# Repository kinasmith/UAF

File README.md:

View this project on [CADLAB.io](https://cadlab.io/node/1009). 

# UAF
This is a storage and sharing area for my projects for the University of Alaska Fairbanks. 
Things are likely in disarray, my apologies.

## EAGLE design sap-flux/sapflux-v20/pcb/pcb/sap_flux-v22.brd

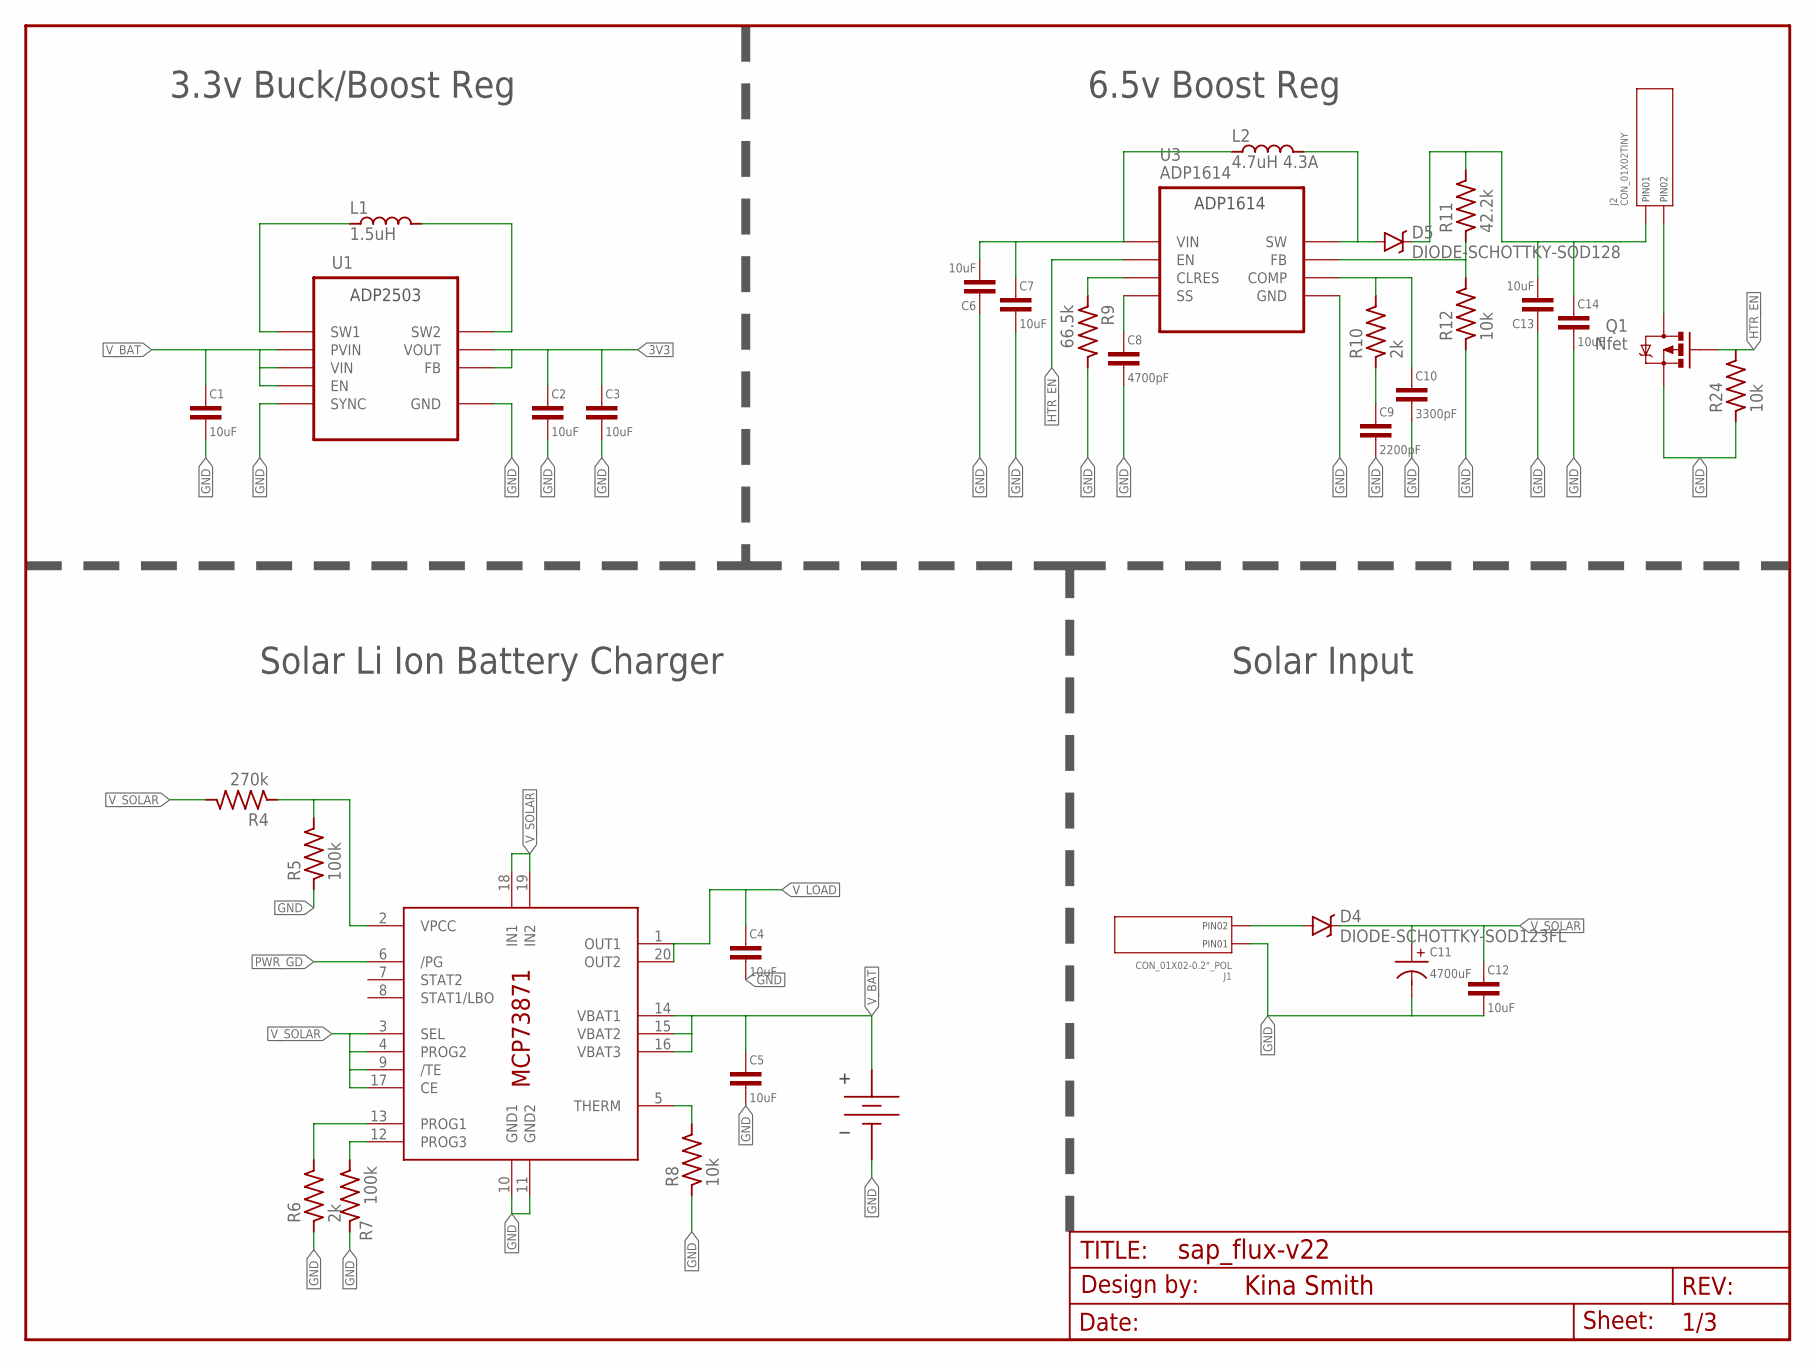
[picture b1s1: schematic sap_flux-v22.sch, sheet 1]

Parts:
BATT1: BATTERY_HOLDER-18650_CLIP; BAT_18650_CLIP
C1, C2, C3, C4, C5, C6, C7, C12, C13, C14: 10uF; C0805-N; PARTNO GRM21BR61C106KE15K
C8: 4700pF; C0603-N; PARTNO GRM188R71C472KA01D
C9: 2200pF; C0603-N; PARTNO GRM188R71C222KA01D
C10: 3300pF; C0603-N; PARTNO C0603C332K4RACTU
C11: 4700uF; CP_TH_5MM
D4: DIODE-SCHOTTKY-SOD123FL; SOD-123FL; PARTNO MBR120VLSFT1G
D5: DIODE-SCHOTTKY-SOD128; SOD128; PARTNO CMS05(TE12L,Q,M)
FRAME1: FRAME-LETTER; CREATIVE_COMMONS
J1: CON_01X02-0.2"_POL; 1X02_SCREWTERM_0.2IN
J2: CON_01X02TINY; 1X02_TINY
L1: 1.5uH; L3030; PARTNO NR3015T1R5N
L2: 4.7uH 4.3A; L8080
Q1: Nfet; SOT23-3; PARTNO DMN2075U-7
R4: 270k; R0603-N; PARTNO RC0603FR-07270KL
R5, R7: 100k; R0603-N; PARTNO RC0603FR-07100KL
R6, R10: 2k; R0603-N; PARTNO RC0603FR-072KL
R8, R12, R24: 10k; R0603-N; PARTNO RC0603FR-0710KL
R9: 66.5k; R0603-N; PARTNO RC0603FR-0766K5L
R11: 42.2k; R0603-N; PARTNO RC0603FR-0742K2L
U1: ADP2503; DFN300X300X80-11N; PARTNO ADP2503ACPZ-3.3-R7
U2: MCP73871; QFN20
U3: ADP1614; DFN300X300X80-11N; PARTNO ADP1614ACPZ-650-R7

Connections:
3V3: C2.1, C3.1, U1.1 (VOUT), U1.10 (FB); also elsewhere on the board
6V5: C13.2, C14.1, D5.C-1 (C), J2.NEG (PIN1), R11.2
6V5_INDUCTOR: D5.A-2 (A), L2.2, U3.6 (SW), U3.7 (SW)
GND: BATT1.NEG_1 (GND), BATT1.NEG_2 (GND), BATT1.NEG_3 (GND), C1.2, C2.2, C3.2, C4.2, C5.2, C6.1, C7.2, C8.2, C9.2, C10.2, C11.NEG, C12.2, C13.1, C14.2, J1.NEG (PIN1), Q1.2 (S), R5.1, R6.1, R7.1, R8.1, R9.2, R12.1, R24.1, U1.3 (GND), U1.7 (SYNC), U1.9 (GND), U1.11 (GND), U2.10 (GND1), U2.11 (GND2), U3.4 (GND), U3.5 (GND), U3.11 (GND); also elsewhere on the board
HTR_EN: Q1.1 (G), R24.2, U3.3 (EN); also elsewhere on the board
unnamed: D4.A, J1.POS (PIN2)
unnamed: R4.1, R5.2, U2.2 (VPCC)
unnamed: R6.2, U2.13 (PROG1)
unnamed: R7.2, U2.12 (PROG3)
unnamed: L1.P$1, U1.4 (SW1)
unnamed: L1.P$2, U1.2 (SW2)
unnamed: R8.2, U2.5 (THERM)
unnamed: J2.POS (PIN2), Q1.3 (D)
unnamed: C8.1, U3.10 (SS)
unnamed: R9.1, U3.9 (CLRES)
unnamed: R11.1, R12.2, U3.2 (FB)
unnamed: C10.1, R10.2, U3.1 (COMP)
unnamed: C9.1, R10.1
PWR_GD: U2.6 (/PG); also elsewhere on the board
V_BAT: BATT1.POS_1 (VBAT), BATT1.POS_2 (VBAT), BATT1.POS_3 (VBAT), C1.1, C5.1, C6.2, C7.1, L2.1, U1.5 (PVIN), U1.6 (EN), U1.8 (VIN), U2.14 (VBAT1), U2.15 (VBAT2), U2.16 (VBAT3), U3.8 (VIN); also elsewhere on the board
V_LOAD: C4.1, U2.1 (OUT1), U2.20 (OUT2)
V_SOLAR: C11.POS, C12.1, D4.C, R4.2, U2.3 (SEL), U2.4 (PROG2), U2.9 (/TE), U2.17 (CE), U2.18 (IN1), U2.19 (IN2)

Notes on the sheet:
3.3v Buck/Boost Reg
6.5v Boost Reg
Solar Li Ion Battery Charger
Solar Input

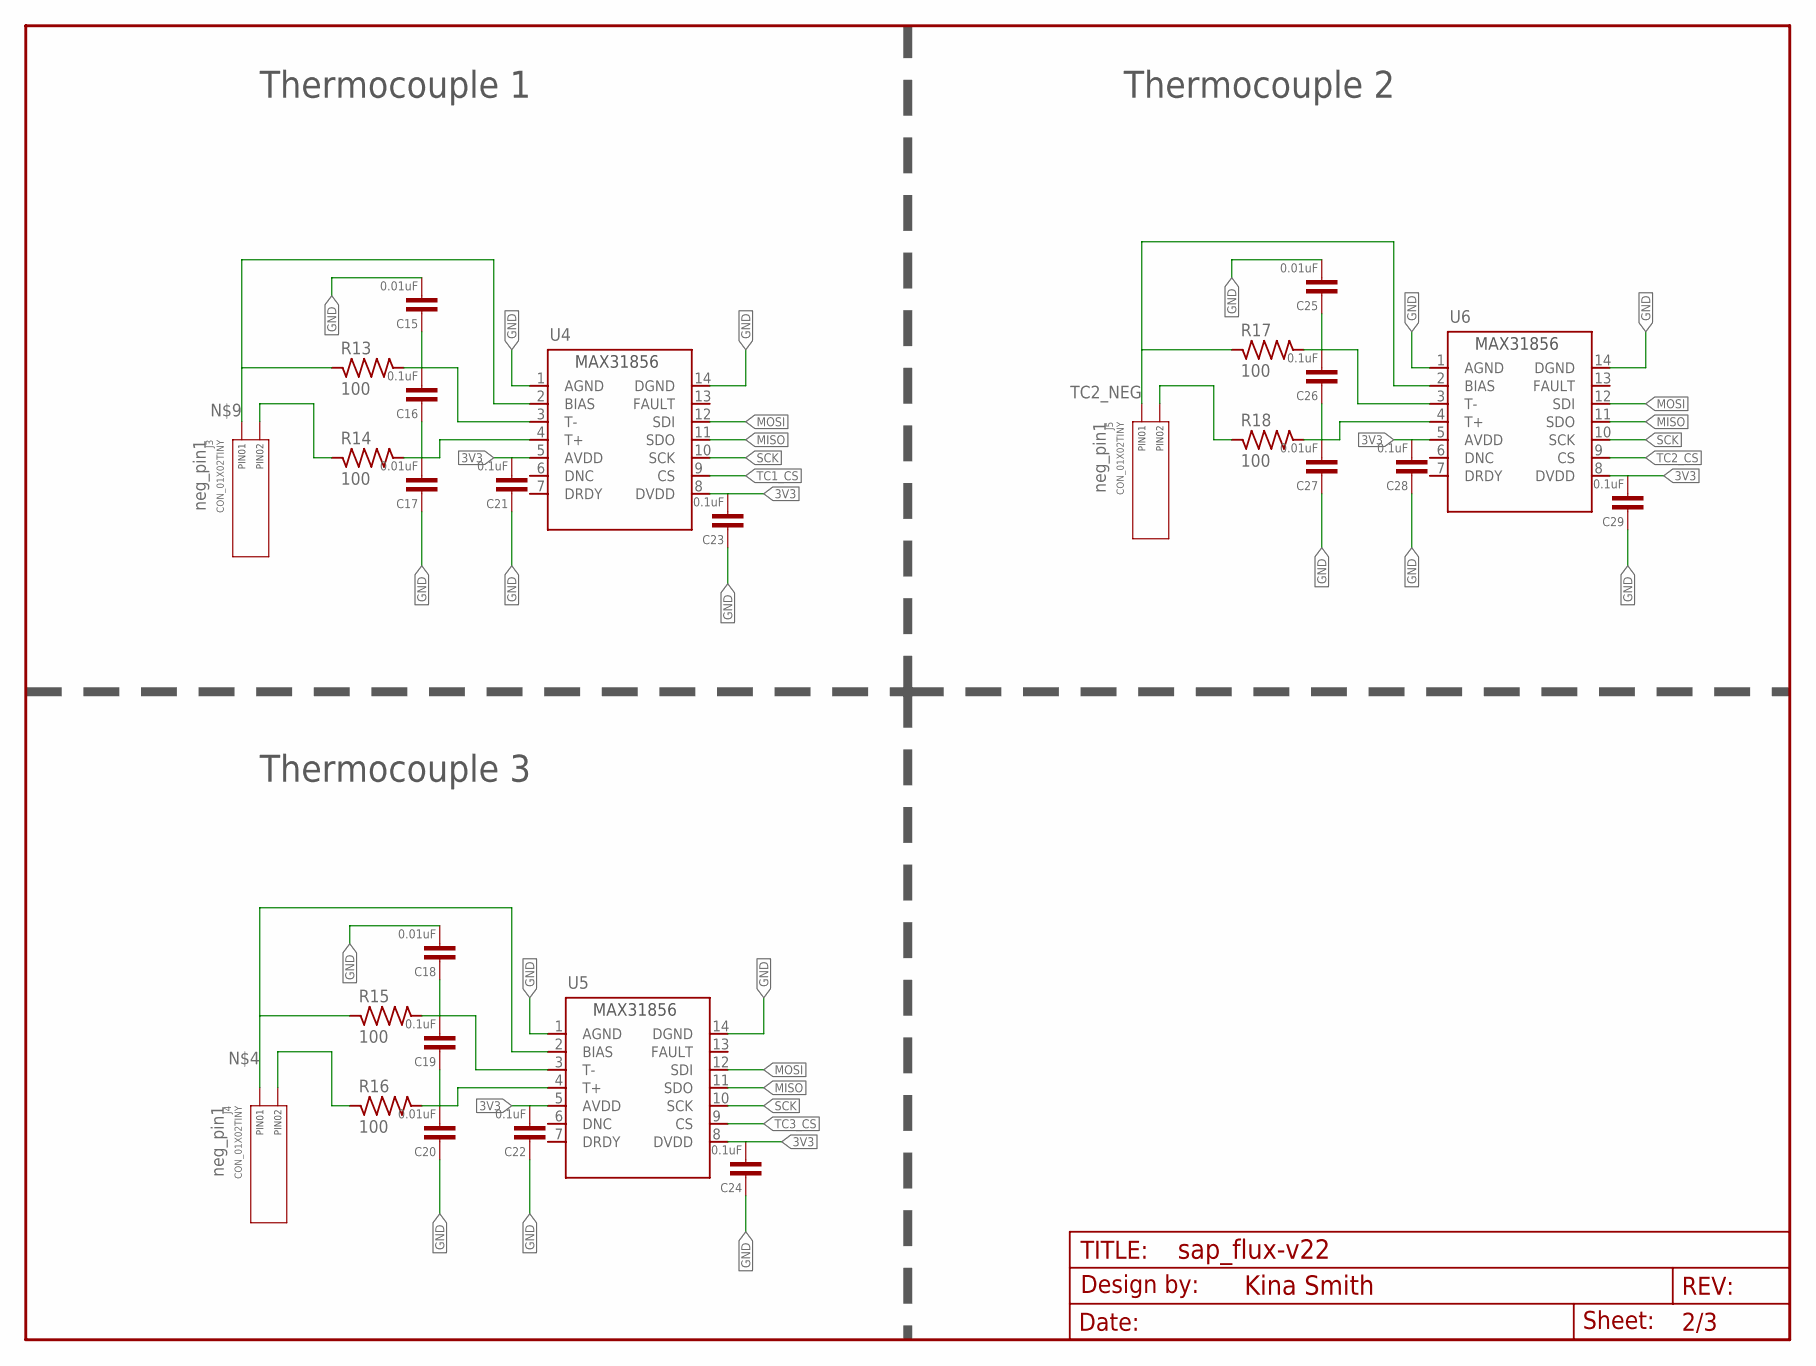
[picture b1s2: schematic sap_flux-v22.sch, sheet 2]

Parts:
C15, C17, C18, C20, C25, C27: 0.01uF; C0603-N; PARTNO GRM188R71C103KA01D
C16, C19, C21, C22, C23, C24, C26, C28, C29: 0.1uF; C0603-N; PARTNO CC0603KRX7R7BB104
FRAME2: FRAME-LETTERNO_PACKAGE; DUMMY
J3, J4, J5: CON_01X02TINY; 1X02_TINY
R13, R14, R15, R16, R17, R18: 100; R0603-N; PARTNO RC0603FR-07100RL
U4, U5, U6: MAX31856MUD+; TSSOP14

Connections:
3V3: C21.2, C22.2, C23.2, C24.2, C28.2, C29.2, U4.5 (AVDD), U4.8 (DVDD), U5.5 (AVDD), U5.8 (DVDD), U6.5 (AVDD), U6.8 (DVDD); also elsewhere on the board
GND: C15.2, C17.1, C18.2, C20.1, C21.1, C22.1, C23.1, C24.1, C25.2, C27.1, C28.1, C29.1, U4.1 (AGND), U4.14 (DGND), U5.1 (AGND), U5.14 (DGND), U6.1 (AGND), U6.14 (DGND); also elsewhere on the board
MISO: U4.11 (SDO), U5.11 (SDO), U6.11 (SDO); also elsewhere on the board
MOSI: U4.12 (SDI), U5.12 (SDI), U6.12 (SDI); also elsewhere on the board
unnamed: J4.POS (PIN2), R16.1
unnamed: J4.NEG (PIN1), R15.1, U5.2 (BIAS)
unnamed: J3.POS (PIN2), R14.1
unnamed: J3.NEG (PIN1), R13.1, U4.2 (BIAS)
unnamed: C19.1, C20.2, R16.2, U5.4 (T+)
unnamed: C18.1, C19.2, R15.2, U5.3 (T-)
unnamed: C16.1, C17.2, R14.2, U4.4 (T+)
unnamed: C15.1, C16.2, R13.2, U4.3 (T-)
unnamed: C25.1, C26.2, R17.2, U6.3 (T-)
unnamed: C26.1, C27.2, R18.2, U6.4 (T+)
SCK: U4.10 (SCK), U5.10 (SCK), U6.10 (SCK); also elsewhere on the board
TC1_CS: U4.9 (CS); also elsewhere on the board
TC2_CS: U6.9 (CS); also elsewhere on the board
TC2_NEG: J5.NEG (PIN1), R17.1, U6.2 (BIAS)
TC2_POS: J5.POS (PIN2), R18.1
TC3_CS: U5.9 (CS); also elsewhere on the board

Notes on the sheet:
Thermocouple 3
Thermocouple 1
Thermocouple 2

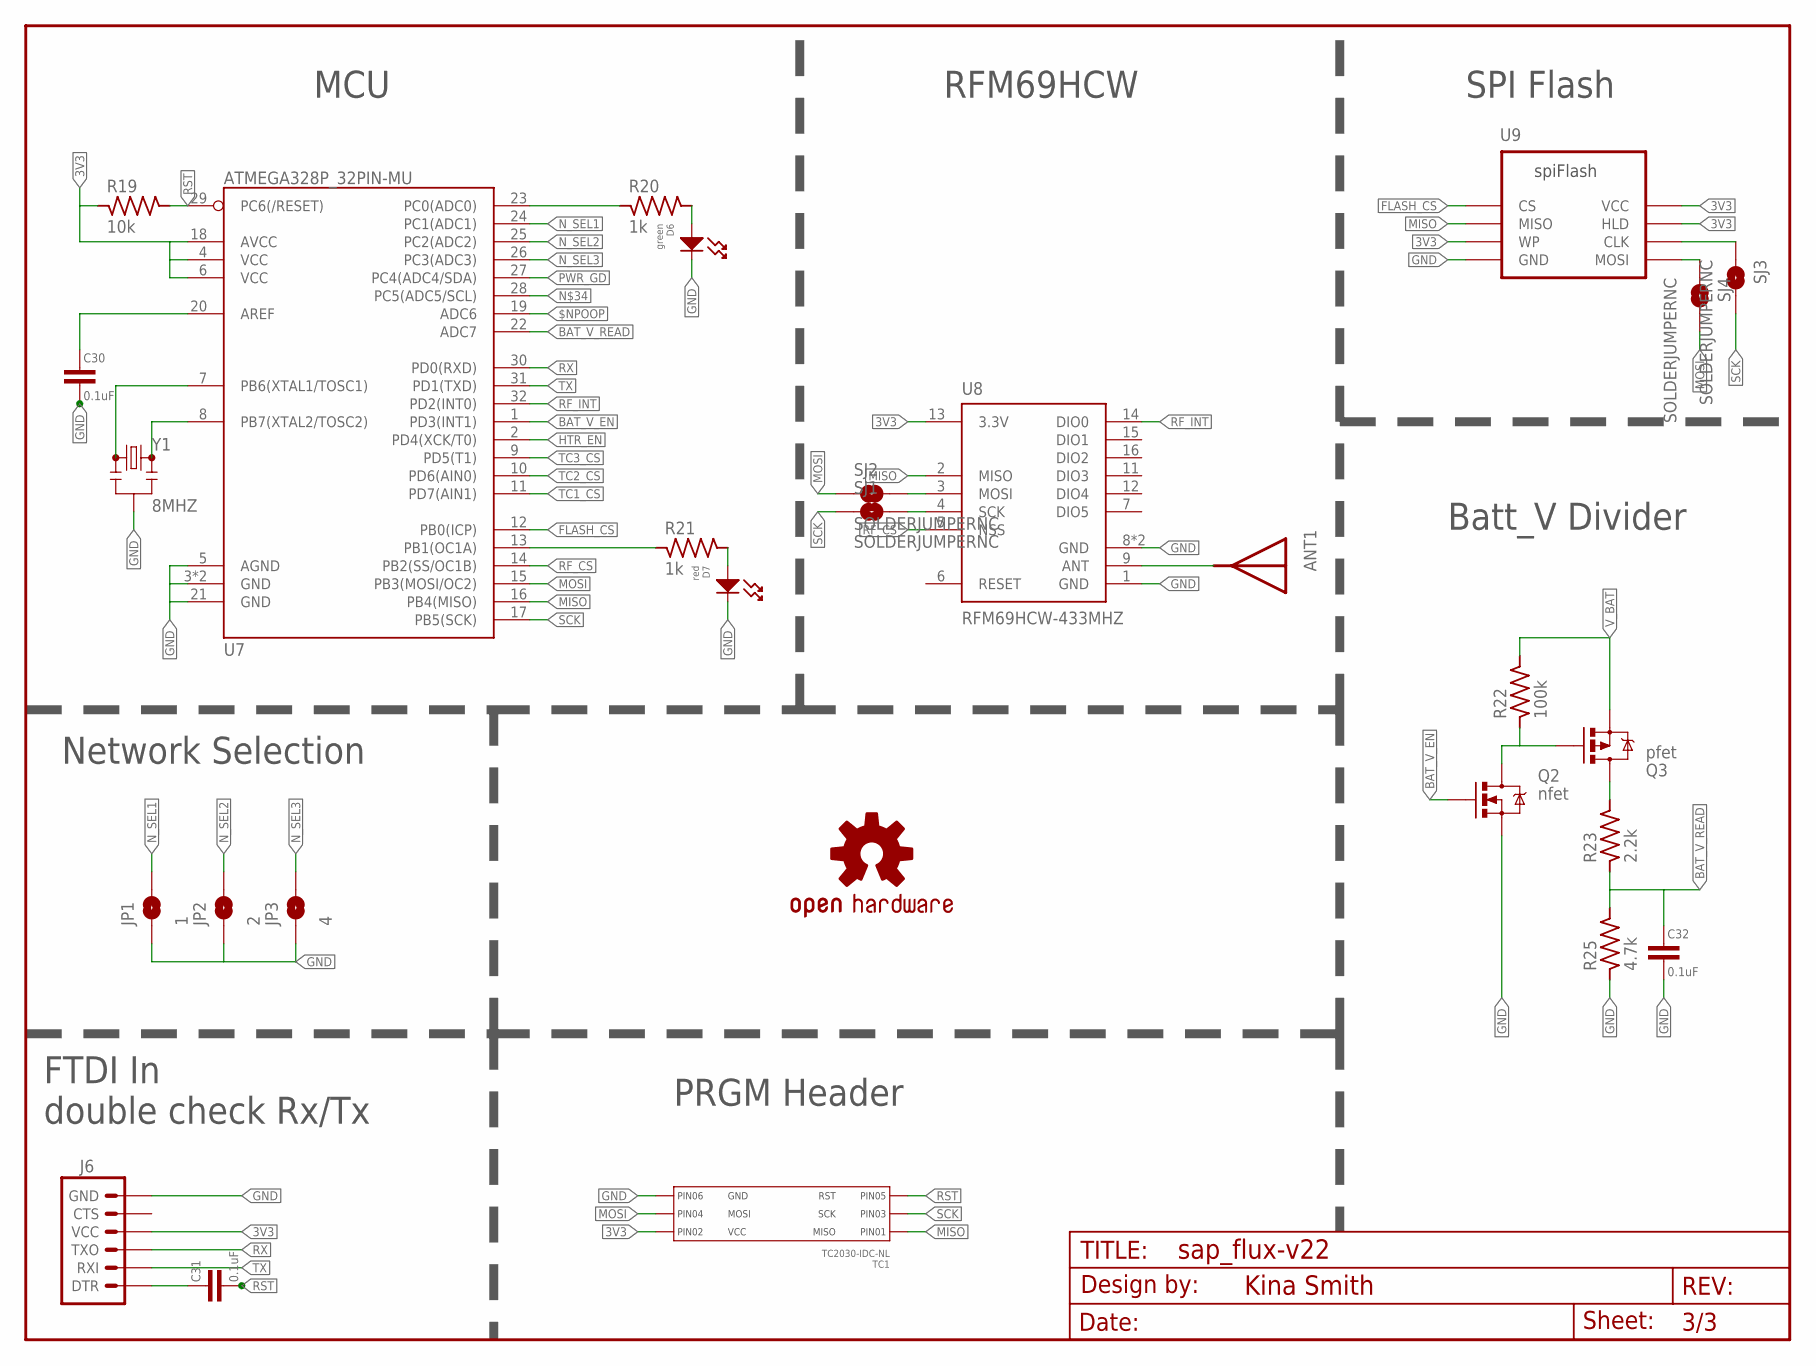
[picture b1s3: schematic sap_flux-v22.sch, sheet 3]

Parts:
ANT1: ANTENNA-433_CHIP; ANT_433_CHIP
C30, C31, C32: 0.1uF; C0603-N; PARTNO CC0603KRX7R7BB104
D6: green; LED0603; PARTNO LTST-C191KGKT
D7: red; LED0603; PARTNO LTST-C191KRKT
FRAME3: FRAME-LETTERNO_PACKAGE; DUMMY
J6: ARDUINO_SERIAL_PROGRAMPTH; 1X06
JP1: 1; PAD-JUMPER-2-NO_YES_SILK
JP2: 2; PAD-JUMPER-2-NO_YES_SILK
JP3: 4; PAD-JUMPER-2-NO_YES_SILK
LOGO1: OSHW-LOGOS-COPPER; OSHW-LOGO-S_COPPER
Q2: nfet; SOT23-3; PARTNO BSS138
Q3: pfet; SOT23-3; PARTNO IRLML2244TRPBF
R19: 10k; R0603-N; PARTNO RC0603FR-0710KL
R20, R21: 1k; R0603-N; PARTNO RC0603FR-071KL
R22: 100k; R0603-N; PARTNO RC0603FR-07100KL
R23: 2.2k; R0603-N; PARTNO RC0603FR-072K2L
R25: 4.7k; R0603-N; PARTNO RC0603FR-074K7L
SJ1, SJ2, SJ3, SJ4: SOLDERJUMPERNC; SJ_2S; PARTNO NA
TC1: TC2030-IDC-NL
U7: ATMEGA328P_32PIN-MU; MLF32_RECTPADS
U8: RFM69HCW-433MHZ; RFM69HCW-XXXS2
U9: WINBOND_FLASH_4MBIT-SOIC; SOIC8
Y1: 8MHZ; RESONATOR-SMD

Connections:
3V3: J6.4 (VCC), R19.1, TC1.P$2 (PIN2), U7.4 (VCC), U7.6 (VCC), U7.18 (AVCC), U8.13 (3.3V), U9.3 (WP), U9.7 (HLD), U9.8 (VCC); also elsewhere on the board
$NPOOP: U7.19 (ADC6)
BAT_V_EN: Q2.1 (G), U7.1 (PD3(INT1))
BAT_V_READ: C32.1, R23.1, R25.2, U7.22 (ADC7)
FLASH_CS: U7.12 (PB0(ICP)), U9.1 (CS)
GND: C30.2, C32.2, D6.CATHODE, D7.CATHODE, J6.6 (GND), JP1.1, JP2.1, JP3.1, Q2.2 (S), R25.1, TC1.P$6 (PIN6), U7.3 (GND), U7.5 (AGND), U7.21 (GND), U7.PAD (GND), U8.1 (GND), U8.8 (GND), U8.10 (GND), U9.4 (GND), Y1.2; also elsewhere on the board
HTR_EN: U7.2 (PD4(XCK/T0)); also elsewhere on the board
MISO: TC1.P$1 (PIN1), U7.16 (PB4(MISO)), U8.2 (MISO), U9.2 (MISO); also elsewhere on the board
MOSI: SJ2.1, SJ4.2, TC1.P$4 (PIN4), U7.15 (PB3(MOSI/OC2)); also elsewhere on the board
unnamed: SJ3.1, U9.6 (CLK)
unnamed: SJ4.1, U9.5 (MOSI)
unnamed: SJ2.2, U8.3 (MOSI)
unnamed: SJ1.2, U8.4 (SCK)
unnamed: ANT1.1, U8.9 (ANT)
unnamed: Q3.3 (D), R23.2
unnamed: Q2.3 (D), Q3.1 (G), R22.1
unnamed: R20.1, U7.23 (PC0(ADC0))
unnamed: C31.1, J6.1 (DTR)
unnamed: D7.ANODE, R21.2
unnamed: D6.ANODE, R20.2
unnamed: U7.8 (PB7(XTAL2/TOSC2)), Y1.3
unnamed: U7.7 (PB6(XTAL1/TOSC1)), Y1.1
unnamed: C30.1, U7.20 (AREF)
N_SEL1: JP1.2, U7.24 (PC1(ADC1))
N_SEL2: JP2.2, U7.25 (PC2(ADC2))
N_SEL3: JP3.2, U7.26 (PC3(ADC3))
PIN_9: R21.1, U7.13 (PB1(OC1A))
PWR_GD: U7.27 (PC4(ADC4/SDA)); also elsewhere on the board
RF_CS: U7.14 (PB2(SS/OC1B)), U8.5 (NSS)
RF_INT: U7.32 (PD2(INT0)), U8.14 (DIO0)
RST: C31.2, R19.2, TC1.P$5 (PIN5), U7.29 (PC6(/RESET))
RX: J6.3 (TXO), U7.30 (PD0(RXD))
SCK: SJ1.1, SJ3.2, TC1.P$3 (PIN3), U7.17 (PB5(SCK)); also elsewhere on the board
TC1_CS: U7.11 (PD7(AIN1)); also elsewhere on the board
TC2_CS: U7.10 (PD6(AIN0)); also elsewhere on the board
TC3_CS: U7.9 (PD5(T1)); also elsewhere on the board
TX: J6.2 (RXI), U7.31 (PD1(TXD))
V_BAT: Q3.2 (S), R22.2; also elsewhere on the board

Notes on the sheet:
Network Selection
FTDI In double check Rx/Tx
PRGM Header
Batt_V Divider
MCU
RFM69HCW
SPI Flash

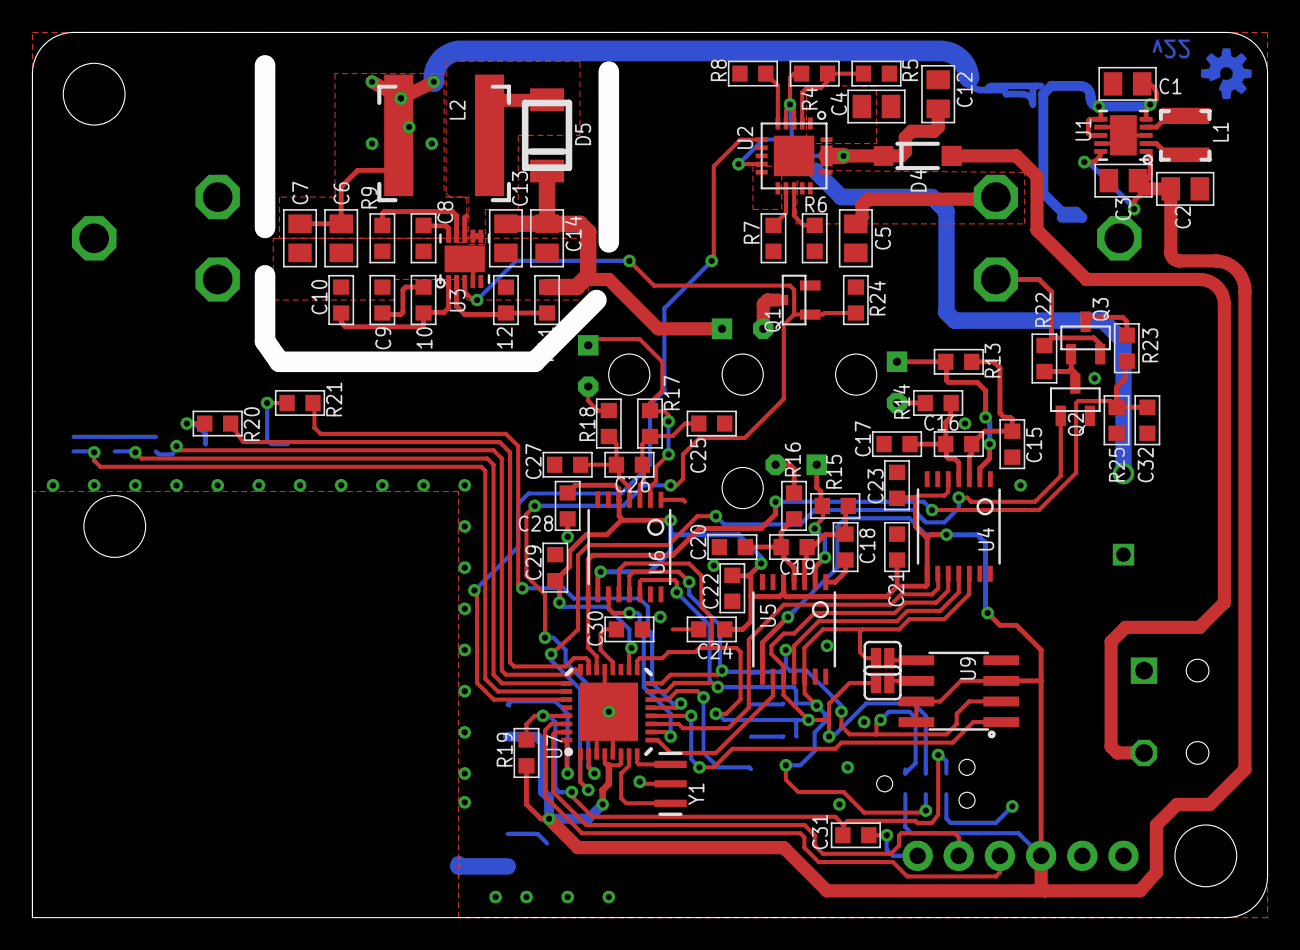
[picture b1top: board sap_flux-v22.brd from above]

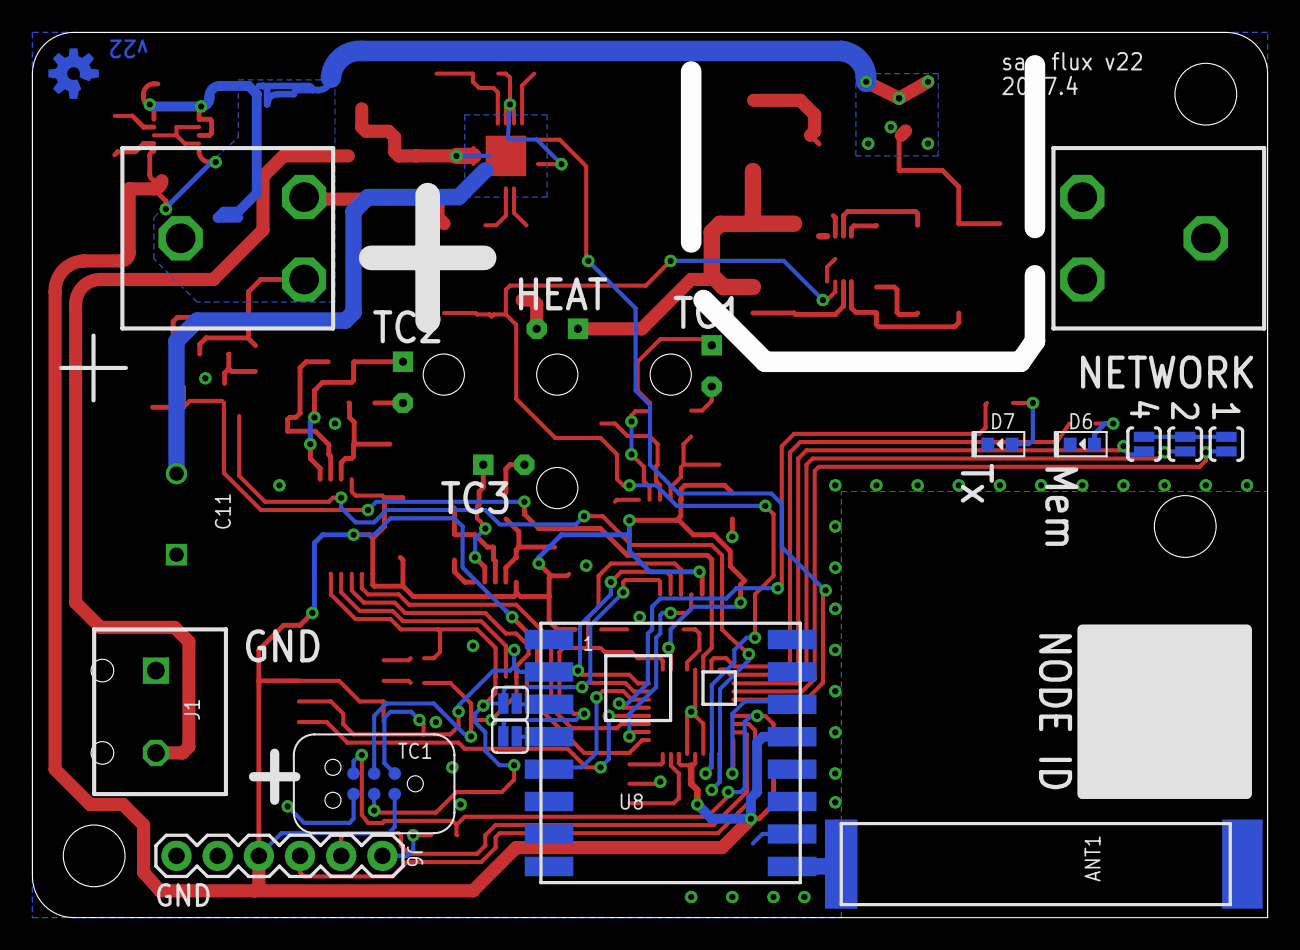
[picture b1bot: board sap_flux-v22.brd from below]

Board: 2 copper layers, 74.9 x 53.3 mm, 93 parts (15 on the bottom side), 66 nets.

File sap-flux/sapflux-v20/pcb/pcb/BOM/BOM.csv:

Supplier Part No,Mfg Part No,Mfg Name,Ref No,Quantity,Value,Description
712-1568-1-ND,0433AT62A0020E,Johanson Technology Inc.,ANT1 ,10,ANTENNA-433_CHIP,433MHz Chip RF Antenna 423MHz ~ 443MHz -4dBi Solder Surface Mount
36-54-ND,54,Keystone Electronics,BATT1 ,10,BATTERY_HOLDER-18650_CLIP,BATTERY CLIP 18MM 18650 CELL
490-6473-1-ND,GRM21BR61C106KE15K,Murata Electronics North America,C1 C2 C3 C4 C5 C6 C7 C12 C13 C14 ,100,10uF,10µF ±10% 16V Ceramic Capacitor X5R 0805 (2012 Metric)
490-11515-1-ND,GRM188R71C472KA01D,Murata Electronics North America,C8 ,10,4700pF,4700pF ±10% 16V Ceramic Capacitor X7R 0603 (1608 Metric)
490-11512-1-ND,GRM188R71C222KA01D,Murata Electronics North America,C9 ,10,2200pF,2200pF ±10% 16V Ceramic Capacitor X7R 0603 (1608 Metric)
399-9065-1-ND,C0603C332K4RACTU,Murata Electronics North America,0C10 ,10,3300pF,3300pF ±10% 16V Ceramic Capacitor X7R 0603 (1608 Metric)
P5130-ND,ECA-1AM472,Panasonic Electronic Components,1C11 ,10,4700uF,"4700µF 10V Aluminum Capacitors Radial, Can 2000 Hrs @ 85°C"
490-1525-1-ND,GRM188R71C103KA01D,Murata Electronics North America,5C15 C17 C18 C20 C25 C27 ,60,0.01uF,10000pF ±10% 16V Ceramic Capacitor X7R 0603 (1608 Metric)
311-1088-1-ND,CC0603KRX7R7BB104,Yageo,6C16 C19 C21 C22 C23 C24 C26 C28 C29 C30 C31 C32 ,120,0.1uF,0.10µF 16V Ceramic Capacitor X7R 0603 (1608 Metric) 
MBR120VLSFT1GOSCT-ND,MBR120VLSFT1G,ON Semiconductor,D4 ,10,DIODE-SCHOTTKY-SOD123FL,Diode Schottky 20V 1A Surface Mount SOD-123FL
CMS05QMCT-ND,"CMS05(TE12L,Q,M)",Toshiba Semiconductor and Storage,D5 ,10,DIODE-SCHOTTKY-SOD128,Diode Schottky 30V 5A Surface Mount M-FLAT (2.4x3.8)
160-1446-1-ND,LTST-C191KGKT,Lite-On Inc.,D6 ,10,green,Green 571nm LED Indication - Discrete 2V 0603 (1608 Metric)
160-1447-1-ND,LTST-C191KRKT,Lite-On Inc.,D7 ,10,red,Red 631nm LED Indication - Discrete 2V 0603 
WM13976-ND,0398890042,"Molex, LLC",J1 ,10,"CON_01X02-0.2_POL""","2 Position Wire to Board Terminal Block Horizontal with Board 0.200"" (5.08mm) Through Hole"
609-3272-ND,68001-106HLF,Amphenol FCI,J6 ,10,,"6 Positions Header, Unshrouded Connector 0.100"" (2.54mm) Through Hole Gold or Gold, GXT"
587-2617-1-ND,NR3015T1R5N,Taiyo Yuden,L1 ,10,1.5uH,1.5µH Shielded Wirewound Inductor 1.82A 48 mOhm Max Nonstandard
587-2972-1-ND,NRS8040T100MJGJ,Taiyo Yuden,L2 ,10,4.7uH 4.3A,10µH Shielded Wirewound Inductor 3.1A 44.2 mOhm Max Nonstandard
DMN2075U-7DICT-ND,DMN2075U-7,Diodes Incorporated,Q1 ,10,Nfet,MOSFET N-CH 20V 4.2A SOT23
BSS138CT-ND,BSS138,Fairchild/ON Semiconductor,Q2 ,10,nfet,MOSFET N-CH 50V 220MA SOT-23
IRLML2244TRPBFCT-ND,IRLML2244TRPBF,Infineon Technologies,Q3 ,10,pfet,MOSFET P-CH 20V 4.3A SOT23
311-270KHRCT-ND,RC0603FR-07270KL,Yageo,R4 ,10,270k,RES SMD 270K OHM 1% 1/10W 0603
311-100KHRCT-ND,RC0603FR-07100KL,Yageo,R5 R7 R22 ,30,100k,RES SMD 100K OHM 1% 1/10W 0603
311-2.00KHRCT-ND,RC0603FR-072KL,Yageo,R6 R10 ,20,2k,RES SMD 2K OHM 1% 1/10W 0603
311-10.0KHRCT-ND,RC0603FR-0710KL,Yageo,R8 R12 R19 R24 ,40,10k,RES SMD 10K OHM 1% 1/10W 0603
311-66.5KHRCT-ND,RC0603FR-0766K5L,Yageo,R9 ,10,66.5k,RES SMD 66.5K OHM 1% 1/10W 0603
311-42.2KHRCT-ND,RC0603FR-0742K2L,Yageo,1R11 ,10,42.2k,RES SMD 42.2K OHM 1% 1/10W 0603
311-100HRCT-ND,RC0603FR-07100RL,Yageo,3R13 R14 R15 R16 R17 R18 ,60,100,RES SMD 100 OHM 1% 1/10W 0603
311-1.00KHRCT-ND,RC0603FR-071KL,Yageo,0R20 R21 ,20,1k,RES SMD 1K OHM 1% 1/10W 0603
311-2.20KHRCT-ND,RC0603FR-072K2L,Yageo,3R23 ,10,2.2k,RES SMD 2.2K OHM 1% 1/10W 0603
311-4.70KHRCT-ND,RC0603FR-074K7L,Yageo,5R25 ,10,4.7k,RES SMD 4.7K OHM 1% 1/10W 0603
ADP2503ACPZ-3.3-R7CT-ND,ADP2503ACPZ-3.3-R7,Analog Devices Inc.,U1 ,10,ADP2503,"Buck-Boost Switching Regulator IC Positive Fixed 3.3V 1 Output 1A (Switch) 10-WFDFN Exposed Pad, CSP"
MCP73871-2AAI/ML,MCP73871-2AAI/ML-ND,Microchip Technology,U2 ,10,,Charger IC Lithium-Ion/Polymer 20-QFN-EP (4x4)
ADP1614ACPZ-650-R7CT-ND,ADP1614ACPZ-650-R7,Analog Devices Inc.,U3 ,10,ADP1614,"Boost Switching Regulator IC Positive Adjustable 2.5V 1 Output 4A (Switch) 10-WFDFN Exposed Pad, CSP"
MAX31856MUD+-ND,MAX31856MUD+,Maxim Integrated,U4 U5 U6 ,30,MAX31856MUD+,IC CONV THERMOCOUPLE 14TSSOP
ATMEGA328P-MU-ND,ATMEGA328P-MU,Atmel,U7 ,10,ATMEGA328P_32PIN-MU,AVR AVR® ATmega Microcontroller IC 8-Bit 20MHz 32KB (16K x 16) FLASH 32-VQFN (5x5)
1568-1391-ND,COM-13910,SparkFun Electronics,U8 ,10,RFM69HCW-433MHZ,RFM69HCW WIRELESS TRANSCEIVER 433MHZ
W25X40CLSNIG-ND,W25X40CLSNIG,Winbond Electronics,U9 ,10,WINBOND_FLASH_4MBIT-SOIC,IC FLASH 4MBIT 104MHZ 8SOIC
490-1195-1-ND,CSTCE8M00G55-R0,Murata Electronics North America,Y1 ,10,8MHZ,8MHz Ceramic Resonator Built in Capacitor 33pF ±0.2% -20°C ~ 80°C Surface Mount

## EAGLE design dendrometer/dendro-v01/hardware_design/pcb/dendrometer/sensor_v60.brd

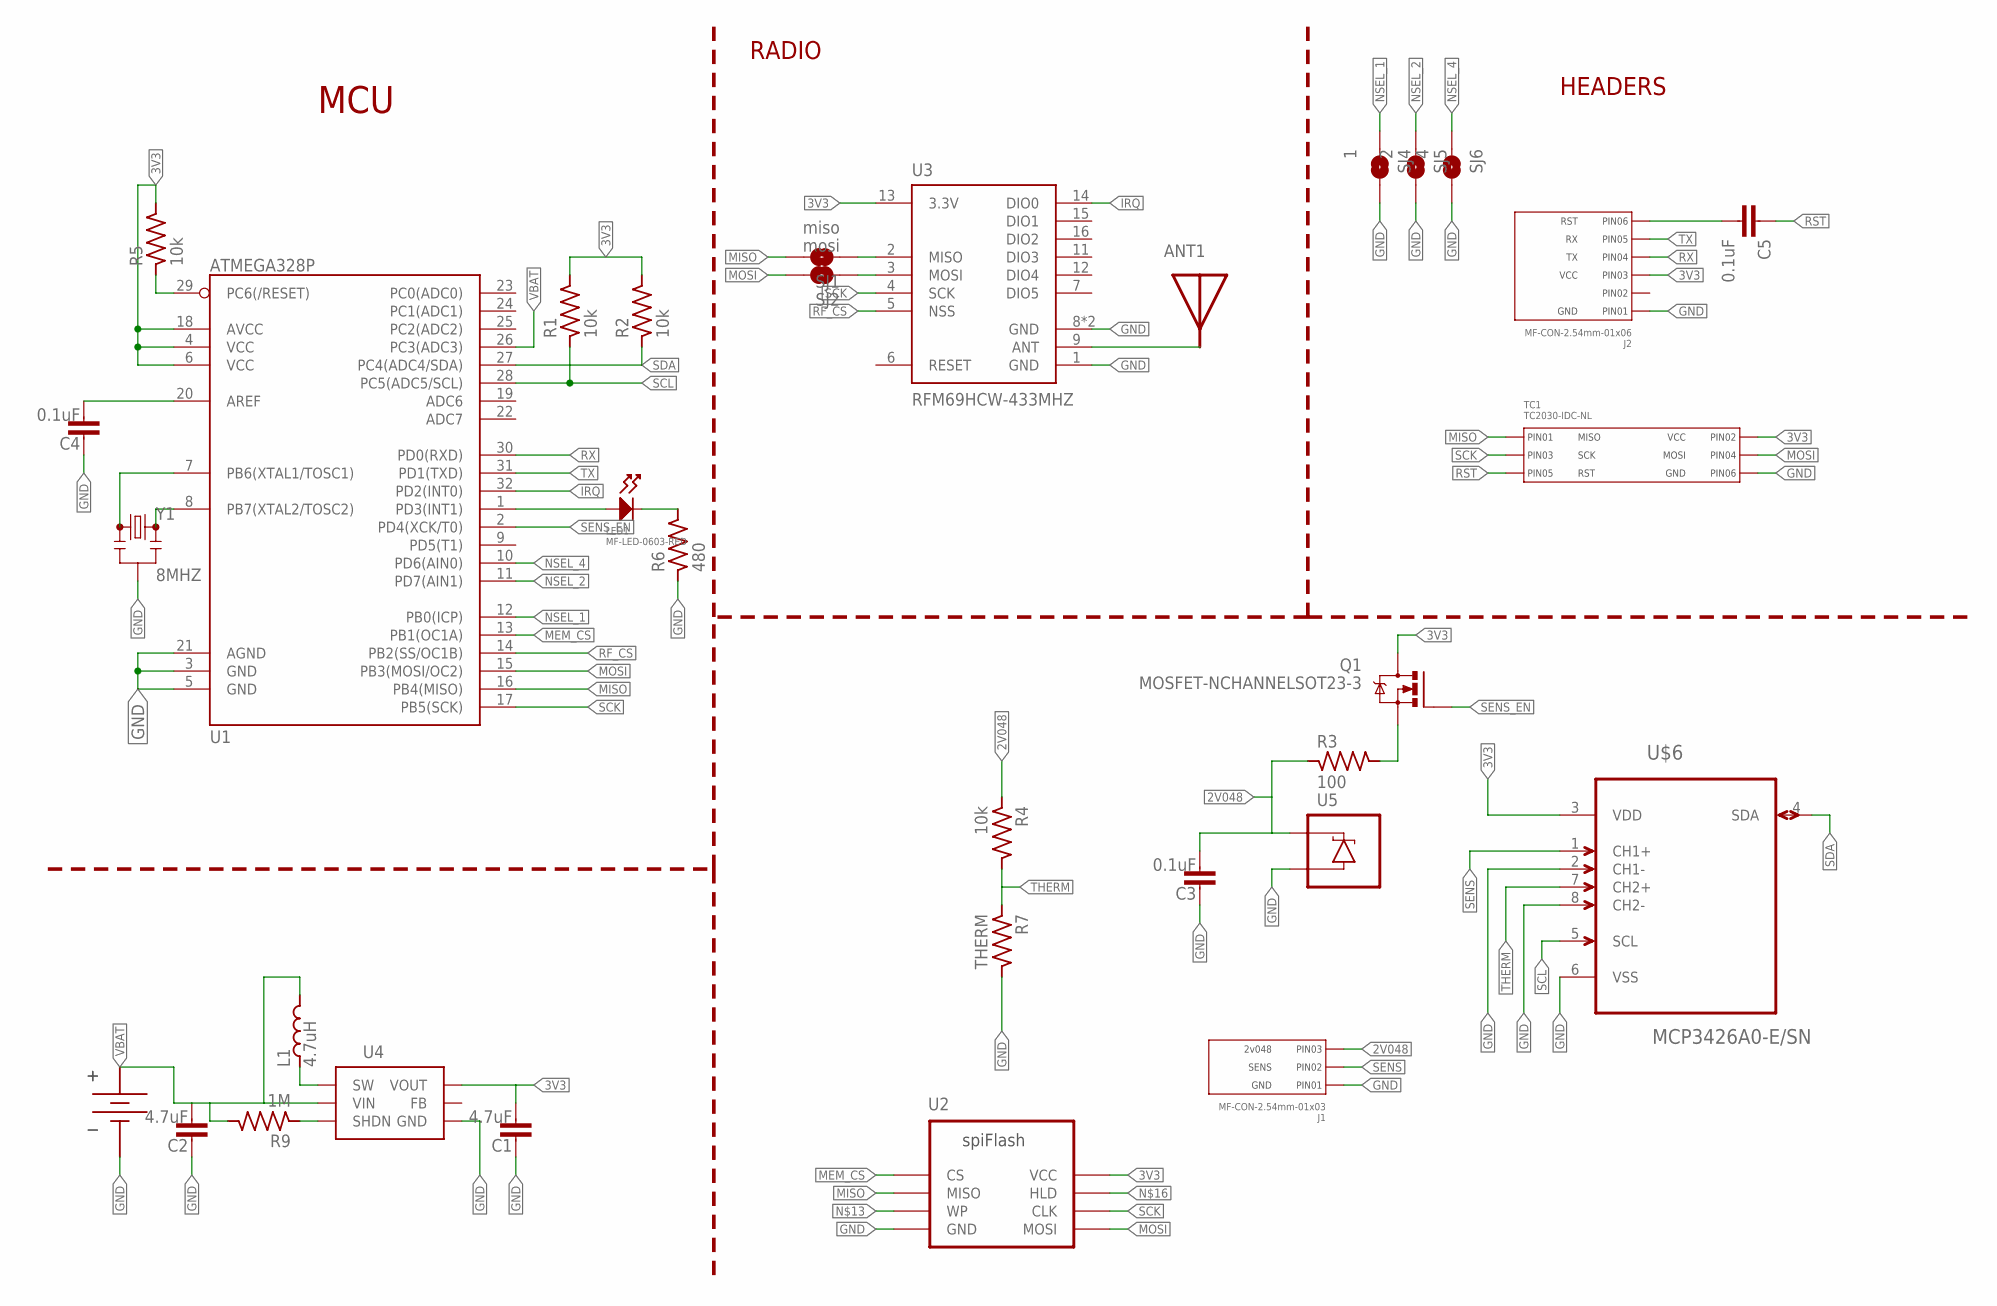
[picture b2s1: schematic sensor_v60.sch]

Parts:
ANT1: ANTENNA-433_CHIP; ANT_433_CHIP
C1, C2: 4.7uF; C0603-N
C3, C4, C5: 0.1uF; C0603-N
J1: MF-CON-2.54mm-01x03; PTH_2.54MM_01X03; PARTNO 0022053031
J2: MF-CON-2.54mm-01x06; PTH_2.54MM_01X06
L1: 4.7uH; L3030
LED1: MF-LED-0603-RED; LED0603
Q1: MOSFET-NCHANNELSOT23-3; SOT23-3
R1, R2, R4, R5: 10k; R0603-N
R3: 100; R0603-N
R6: 480; R0603-N
R7: THERM; R0603-N; PARTNO FIND PART!!
R9: 1M; R0603-N
SJ1: miso; SJ_2S-NOTRACE
SJ2: mosi; SJ_2S-NOTRACE
SJ4: 1; SJ_2S-NOTRACE
SJ5: 2; SJ_2S-NOTRACE
SJ6: 4; SJ_2S-NOTRACE
TC1: TC2030-IDC-NL
U1: ATMEGA328P; TQFP32
U2: WINBOND_FLASH_4MBIT-SOIC; SOIC8
U3: RFM69HCW-433MHZ; RFM69HCW-XXXS2
U4: AAT1217-SOT23-6; SOT23-6
U5: LM4040-SOT-23-3; SOT23-3
U$1: KEYSTONEAAHOLDER_2CELL
U$6: MCP3426A0-E/SN; SOIC127P600X175-8N
Y1: 8MHZ; RESONATOR-SMD

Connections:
2V048: C3.2, J1.P$3 (PIN3), R3.1, R4.1, U5.1 (C)
3V3: C1.2, J2.P$3 (PIN3), Q1.3 (D), R1.2, R2.2, R5.2, TC1.P$2 (PIN2), U1.4 (VCC), U1.6 (VCC), U1.18 (AVCC), U2.8 (VCC), U3.13 (3.3V), U4.5 (VOUT), U$6.3 (VDD)
GND: C1.1, C2.1, C3.1, C4.1, J1.P$1 (PIN1), J2.P$1 (PIN1), R6.1, R7.2, SJ4.2, SJ5.2, SJ6.2, TC1.P$6 (PIN6), U1.3 (GND), U1.5 (GND), U1.21 (AGND), U2.4 (GND), U3.1 (GND), U3.8 (GND), U3.10 (GND), U4.2 (GND), U5.2 (A), U$1.P$2 (GND), U$6.2 (CH1-), U$6.6 (VSS), U$6.8 (CH2-), Y1.2
IRQ: U1.32 (PD2(INT0)), U3.14 (DIO0)
MEM_CS: U1.13 (PB1(OC1A)), U2.1 (CS)
MISO: SJ1.2, TC1.P$1 (PIN1), U1.16 (PB4(MISO)), U2.2 (MISO)
MOSI: SJ2.2, TC1.P$4 (PIN4), U1.15 (PB3(MOSI/OC2)), U2.5 (MOSI)
unnamed: R9.1, U4.4 (SHDN)
unnamed: ANT1.1, U3.9 (ANT)
unnamed: LED1.ANODE, U1.1 (PD3(INT1))
unnamed: C4.2, U1.20 (AREF)
unnamed: LED1.CATHODE, R6.2
unnamed: L1.P$1, U4.1 (SW)
unnamed: U1.7 (PB6(XTAL1/TOSC1)), Y1.1
unnamed: U1.8 (PB7(XTAL2/TOSC2)), Y1.3
unnamed: SJ1.1, U3.2 (MISO)
unnamed: C5.2, J2.P$6 (PIN6)
unnamed: SJ2.1, U3.3 (MOSI)
unnamed: Q1.2 (S), R3.2
NSEL_1: SJ4.1, U1.12 (PB0(ICP))
NSEL_2: SJ5.1, U1.11 (PD7(AIN1))
NSEL_4: SJ6.1, U1.10 (PD6(AIN0))
RF_CS: U1.14 (PB2(SS/OC1B)), U3.5 (NSS)
RST: C5.1, R5.1, TC1.P$5 (PIN5), U1.29 (PC6(/RESET))
RX: J2.P$4 (PIN4), U1.30 (PD0(RXD))
SCK: TC1.P$3 (PIN3), U1.17 (PB5(SCK)), U2.6 (CLK), U3.4 (SCK)
SCL: R1.1, U1.28 (PC5(ADC5/SCL)), U$6.5 (SCL)
SDA: R2.1, U1.27 (PC4(ADC4/SDA)), U$6.4 (SDA)
SENS: J1.P$2 (PIN2), U$6.1 (CH1+)
SENS_EN: Q1.1 (G), U1.2 (PD4(XCK/T0))
THERM: R4.2, R7.1, U$6.7 (CH2+)
TX: J2.P$5 (PIN5), U1.31 (PD1(TXD))
VBAT: C2.2, L1.P$2, R9.2, U1.26 (PC3(ADC3)), U4.6 (VIN), U$1.P$1 (VBAT)

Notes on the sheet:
MCU
RADIO
HEADERS

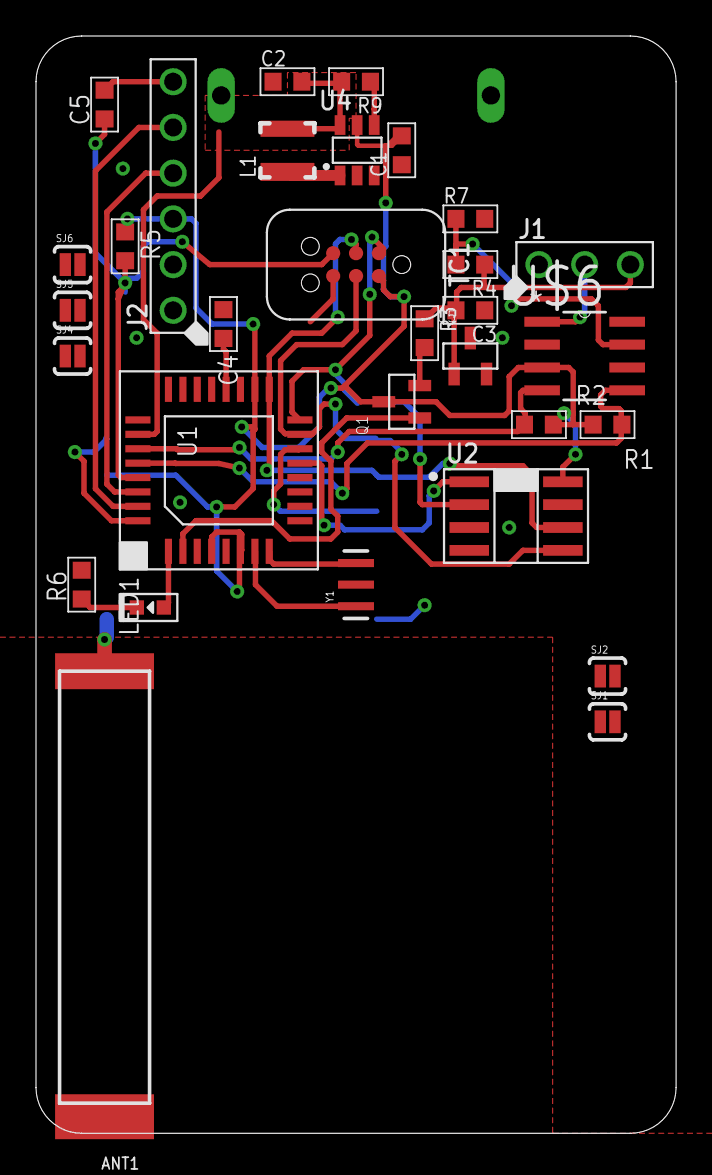
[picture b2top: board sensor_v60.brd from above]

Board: 2 copper layers, 35.6 x 61.0 mm, 33 parts (1 on the bottom side), 33 nets.

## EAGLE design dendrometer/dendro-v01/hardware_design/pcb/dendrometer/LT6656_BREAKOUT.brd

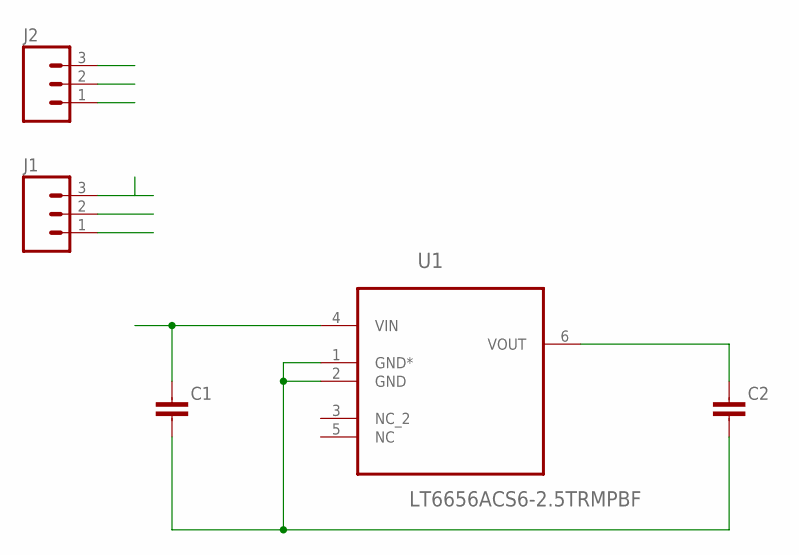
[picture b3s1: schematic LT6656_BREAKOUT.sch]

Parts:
C1, C2: CAPACITOR0603-N; C0603-N
J1, J2: M03PTH; 1X03
U1: LT6656ACS6-2.5TRMPBF; SOT95P280X100-6N

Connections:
GND: C1.2, C2.2, J1.1, J2.1, U1.1 (GND*), U1.2 (GND)
OUT: J1.2, J2.2
VIN: C1.1, J1.3, U1.4 (VIN)
VOUT: C2.1, J2.3, U1.6 (VOUT)

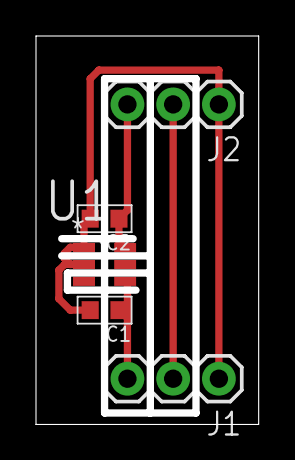
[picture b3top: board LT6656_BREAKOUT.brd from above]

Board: 2 copper layers, 12.0 x 21.2 mm, 5 parts (0 on the bottom side), 4 nets.

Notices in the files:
parts and their libraries:
SparkFun-Connectors: Licensing: Creative Commons ShareAlike 4.0 International - https://creativecommons.org/licenses/by-sa/4.0
My_Aesthetics: Released under the Creative Commons Attribution Share-Alike 4.0 License
My_Aesthetics: https://creativecommons.org/licenses/by-sa/4.0
